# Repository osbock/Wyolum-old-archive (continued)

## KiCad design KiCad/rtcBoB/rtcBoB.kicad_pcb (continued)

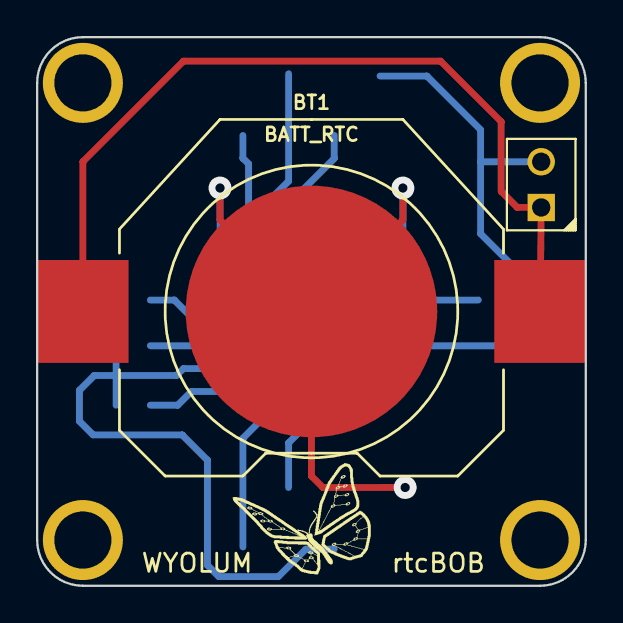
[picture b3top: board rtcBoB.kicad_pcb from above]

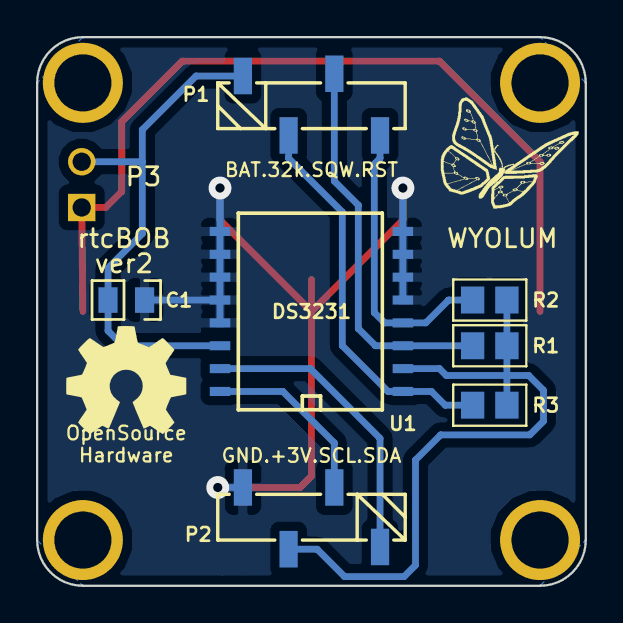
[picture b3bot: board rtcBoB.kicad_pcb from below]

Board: 2 copper layers, 30.5 x 30.5 mm, 15 parts (8 on the bottom side), 9 nets.

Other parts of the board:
G1, G1#2: Logo-WL3

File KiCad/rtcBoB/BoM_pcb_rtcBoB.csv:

"Id";"Designator";"Package";"Quantity";"Designation";"Supplier and ref";
1;"P3";"pin_strip_2";1;"CONN_2";;;
2;"U1";"DS3231";1;"DS3231";;;
3;"H4,H3,H2,H1";"vite_2mm5";4;"CONN_1";;;
4;"P1";"Sck-04-F-SMT";1;"CDOT1";;;
5;"P2";"Sck-04-F-SMT";1;"CDOT2";;;
6;"R1,R2,R3";"r_0805";3;"10k";;;
7;"C1";"c_0805";1;"100n";;;
8;"G1,G1";"Logo-WL3";2;"Logo-WL3";;;
9;"G***";"OSHW_6mm";1;"LOGO";;;
10;"BT1";"CR2032_SMD";1;"BATT_RTC";;;

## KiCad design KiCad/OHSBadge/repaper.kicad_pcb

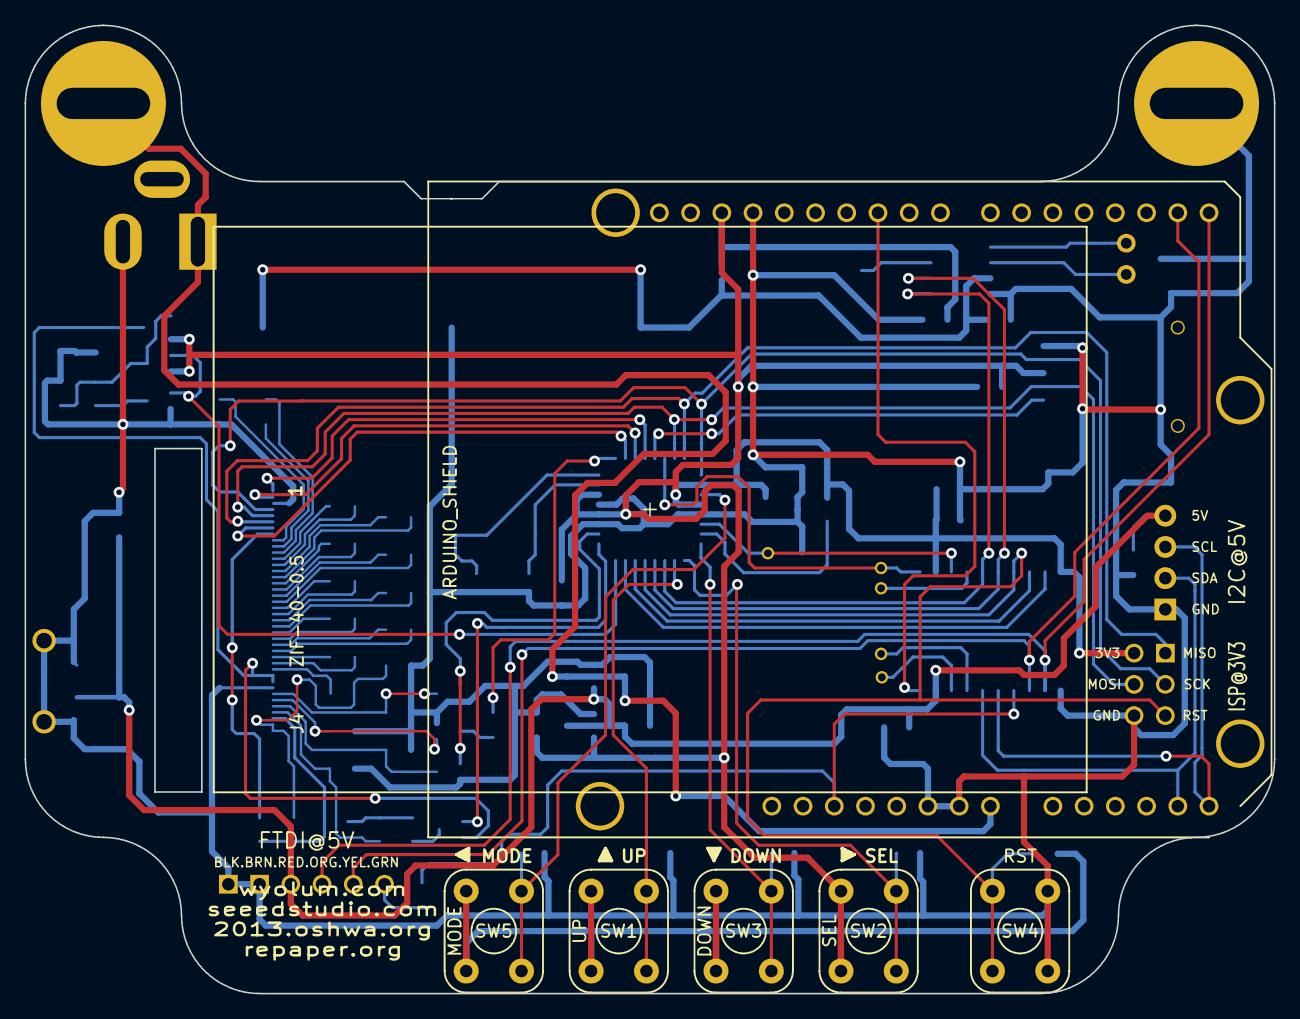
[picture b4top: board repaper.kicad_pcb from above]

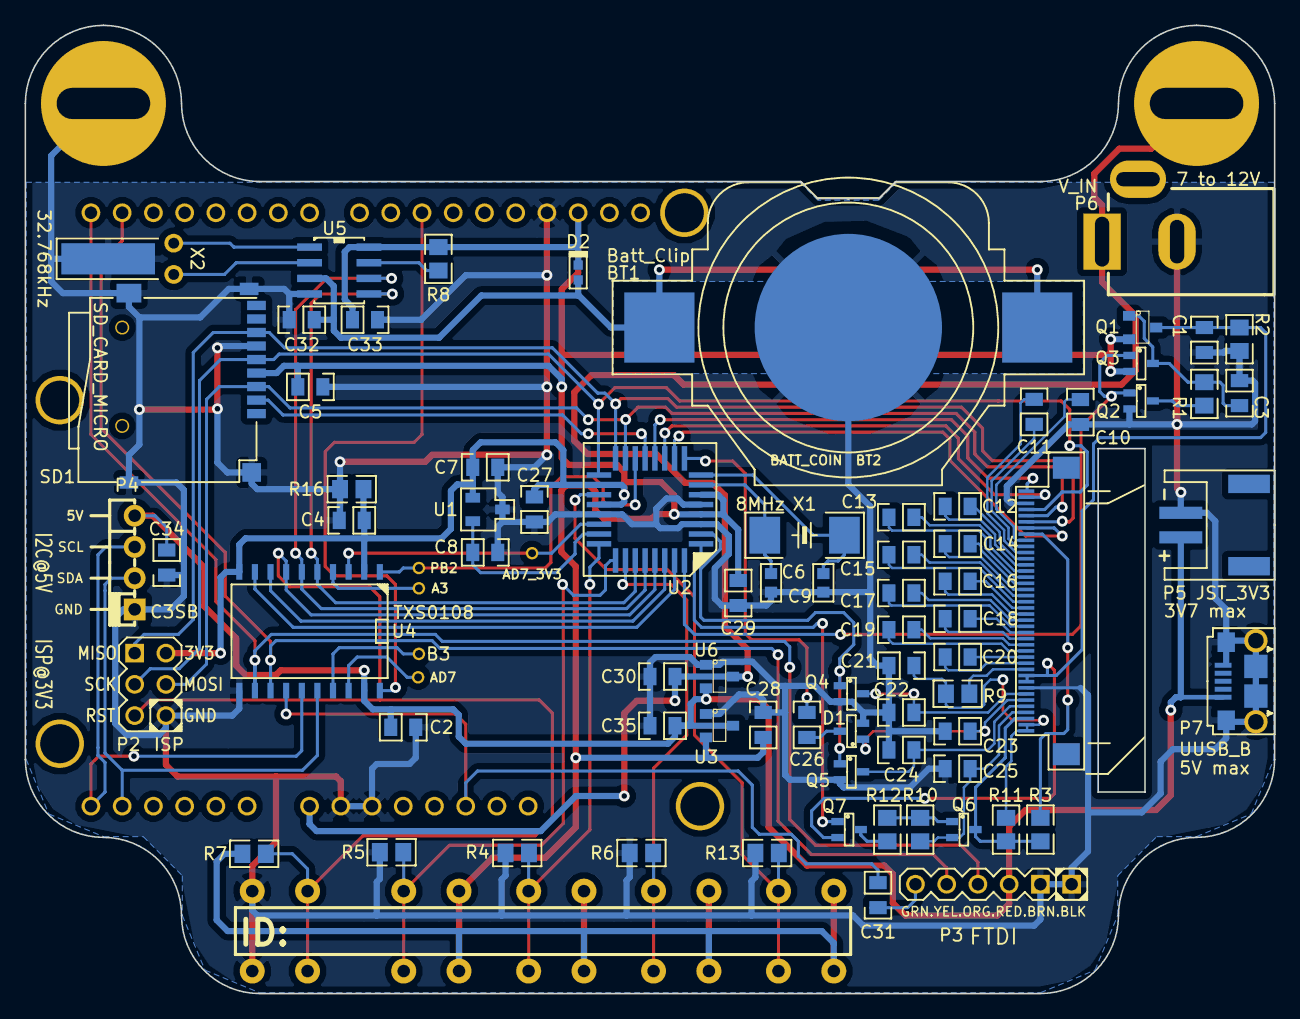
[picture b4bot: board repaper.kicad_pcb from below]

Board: 2 copper layers, 101.6 x 78.7 mm, 90 parts (80 on the bottom side), 78 nets.

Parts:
A3: I/O
AD7, AD7_3V3: I/O
B3: I/O
BT1: Batt_Clip; CR2450_SMD
BT2: BATT_COIN; CR2032
C1, C11, C12, C14, C17, C18, C19, C20, C24, C25, C28, C30, C35: 2.2u,16V; c_0805
C2, C3, C4, C5, C8, C26, C27, C29, C31, C32, C33, C34: 0.1u,16V; c_0805
C6, C9: 22pF; c_0603
C7: 1u,16V; c_0805
C10: 2.2u,10V; c_0805
C13, C15, C16, C22, C23: 2.2u,25V; c_0805
C21: 1u,10V; c_0805
D1: BAT54SW; SOT323
D2: DB2S20500L; d_VMD2
H1, H2: I/O; vite_3mm
J4: ZIF-40-0.5; ZIF-40-0.5-M_Hirose
P1: PCB
P2: ISP; Header_ISP
P3: FTDI; Header_FTDI
P4: C3SB; pin_strip_4-90
P5: JST_3V3; CONN_JST-2_SMD
P6: V_IN; JACK_ALIM
P7: UUSB_B; USB_B_Micro
PB2: I/O
Q1: DMG2301U-7; SOT23
Q2, Q4, Q5, Q6: 2N7002KW; SOT323
Q3, Q7: BSS84W; SOT323
R1, R2: 33k; r_0805
R3: 0R(NC); r_0805
R4, R5, R6, R7, R8, R13, R16: 10k; r_0805
R9: 2k; r_0805
R10, R11, R12: 100k; r_0805
SD1: SD_CARD_MICRO; SD_Micro
SHIELD1: ARDUINO_SHIELD; ARDUINO_SHIELD_040pins
SW1: UP; SW-PB
SW2: SEL; SW-PB
SW3: DOWN; SW-PB
SW4: RST; SW-PB
SW5: MODE; SW-PB
U1: MCP9700AT-E/TT; SOT23-3-Temp
U2: ATMEGA328-AU-ND; TQFP32
U3: MCP1700T-33; SOT23
U4: TXS0108; SO20L
U5: DS1307; SO8E
U6: MCP1702T-50; SOT23
X1: 8MHz; Xtal_SMD
X2: 32.768kHz; XTAL_3

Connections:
/3V3: C4.1, C5.1, C7.2, C27.2, C28.1, C29.1, C33.1, D2.2, P2.5, Q1.2, Q3.2, R7.2, R8.2, R16.2, SD1.4, SHIELD1.AREF, SW1.2, SW2.2, SW3.2, SW5.2, U1.1, U2.4, U2.6, U2.18, U2.20, U3.2, U4.2, U4.10, U5.8
//EPD_CS_3V3: J4.1, U2.12
//RESET_3V3: J4.7, U2.10
/AD7: AD7.1, U4.18
/AD7_3V3: AD7_3V3.1, U2.22, U4.3
/BATT_3V: BT1.+, C32.1, D2.1, U5.3
/BORDER: J4.38, Q6.3, R3.2, R11.1
/BORDER_CONTROL: Q7.1, U2.1
/BUSY_3V3: J4.2, U2.11
/C11M: C20.1, J4.28
/C11P: C20.2, J4.29
/C12M: C19.1, J4.26
/C12P: C19.2, J4.27
/C13M: C18.1, J4.24
/C13P: C18.2, J4.25
/C14M: C17.1, J4.22
/C14P: C17.2, J4.23
/C15M: C16.1, J4.20
/C15P: C16.2, J4.21
/C16M: C15.1, J4.18
/C16P: C15.2, J4.19
/C21M: C14.1, J4.16
/C21P: C14.2, J4.17
/C31M: C13.1, J4.14
/C31P: C13.2, J4.15
/C41M: C12.2, J4.13
/C41P: C12.1, J4.12
/C42M: C11.2, J4.11
/C42P: C11.1, J4.10
/DISCHARGE: Q4.1, Q5.1, U2.2
/DOWN: R4.2, SW3.1, U2.24
/DTR: C31.2, P3.6
/MODE: R13.2, SW5.1, U2.19
/PANEL_ON: Q2.1, Q3.1, U2.32
/PWM: C26.2, U2.9
/RST: C31.1, SHIELD1.RST, U4.14
/RST_3V3: P2.2, R7.1, SW4.2, U2.29, U4.7
/RXD: P3.4, SHIELD1.0, U4.12
/RXD_3V3: U2.30, U4.8
/SCL: P4.2, SHIELD1.AD5, U4.15
/SCL_3V3: U2.28, U4.6, U5.6
/SDA: P4.3, SHIELD1.AD4, U4.16
/SDA_3V3: U2.27, U4.5, U5.5
/SD_CS_3V3: SD1.2, U2.13
/SEL: R5.2, SW2.1, U2.25
/SPI_CLK_3V3: J4.4, P2.4, SD1.5, U2.17
/SPI_MISO_3V3: J4.6, P2.6, SD1.7, U2.16
/SPI_MOSI_3V3: J4.5, P2.3, SD1.3, U2.15
/SPI_SS: SHIELD1.10, U4.20
/SPI_SS_3V3: PB2.1, U2.14, U4.1
/SQW: R8.1, U5.7
/TEMPERATURE: C8.1, U1.2, U2.23
/TXD: P3.5, SHIELD1.1, U4.13
/TXD_3V3: U2.31, U4.9
/UP: R6.2, SW1.1, U2.26
/VCC5V: C2.1, C34.1, C35.1, P3.3, P4.1, P5.1, P7.1, U3.3, U4.19, U6.2
/VCC_T: C1.2, J4.31, J4.32, Q1.3, Q7.2, R2.1
/VCL: C10.2, J4.9
/VCOM: C21.2, J4.39, J4.40, R9.2, R11.2
/VCOM_DRIVER: J4.30, R9.1
/VDH: C24.1, J4.36, Q5.3
/VDL: C25.1, J4.37, Q6.2, R10.2
/VGH: C22.1, J4.34, Q4.3
/VGL: C23.1, D1.1, J4.35
/V_IN: C30.1, H1.1, P6.1, SHIELD1.V_IN, U6.3
GND: BT1.-, C1.1, C2.2, C3.1, C4.2, C5.2, C6.1, C7.1, C8.2, C9.1, C10.1, C21.1, C22.2, C23.2, C24.2, C25.2, C27.1, C28.2, C29.2, C30.2, C32.2, C33.2, C34.2, C35.2, D1.2, H2.1, J4.3, J4.33, P2.1, P3.1, P3.2, P4.4, P5.2, P6.2, P7.5, P7.T1, P7.T2, P7.T3, P7.T4, P7.T5, P7.T6, Q2.2, Q4.2, Q5.2, R2.2, R4.1, R5.1, R6.1, R13.1, R16.1, SD1.6, SD1.G1, SD1.G2, SD1.G3, SD1.G4, SHIELD1.GND1, SHIELD1.GND2, SHIELD1.GND3, SW4.1, U1.3, U2.3, U2.5, U2.21, U3.1, U4.11, U5.4, U6.1, X2.3
unnamed: Q2.3, R1.1
unnamed: B3.1, U4.17
unnamed: A3.1, U4.4
unnamed: C3.2, Q1.1, Q3.3, R1.2
unnamed: Q6.1, R10.1, R12.1
unnamed: Q7.3, R12.2
unnamed: C26.1, D1.3
unnamed: J4.8, R3.1
unnamed: U5.2, X2.2
unnamed: U5.1, X2.1
unnamed: C9.2, U2.8, X1.1
unnamed: C6.2, U2.7, X1.2

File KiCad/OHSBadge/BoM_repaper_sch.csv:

I/O	6	"A3 AD7 AD7_3V3 B3 PB2 U5/7"	I/O
BATT_COIN	1	"BT2"	CR2032	BATTERY LITHIUM COIN 3V 20MM	Lithium, 3V, 225mAh	CR2032	Panasonic - BSG	CR2032	Digikey	P189-ND
Batt_Clip	1	"BT1"	CR2450_SMD	HOLDER BATTERY COIN 20MM DIA THM	Coin Cell, Retainer	Coin, 20.0mm	Keystone Electronics	3003	Digikey	3003K-ND
22pF	2	"C6 C9"	c_0603	0603/0.1uF/16V
0.1u,16V	9	"C2 C4 C5 C27 C29 C31 C32 C33 C34"	c_0805	0603/0.1uF/16V
0.1u,16V	1	"C3"	c_0805	0402/0.1uF/16V/Y5V
0.1u,16V	1	"C8"	c_0805	0603/0.1uF/16V	DNP
0.1u,16V	1	"C26"	c_0805	0603/100n/16V/X7R
1u,16V	1	"C7"	c_0805	1u/10V/X7R
1u,10V	1	"C21"	c_0805	1u/10V/X7R
2.2u,16V	1	"C1"	c_0805	0805/2.2u/10V/Y5V
2.2u,10V	1	"C10"	c_0805	0805/2.2u/10V/Y5V
2.2u,16V	9	"C11 C12 C14 C17 C18 C19 C20 C24 C25"	c_0805	0805/2.2u/16V/Y5V
2.2u,25V	5	"C13 C15 C16 C22 C23"	c_0805	0805/2.2u/25V/Y5V
2.2u,16V	3	"C28 C30 C35"	c_0805	0805/2.2uF/16V/Y5V
DB2S20500L	1	"D2"	d_VMD2
BAT54SW	1	"D1"	SOT323
OSHW	1	"G4"	OSHW_logo
repaper	1	"G3"	repaper_logo
seeed	1	"G2"	seeed
WYO	1	"G1"	wyo_logo
I/O	2	"H1 H2"	vite_3mm
ZIF-40-0.5	1	"J4"	ZIF-40-0.5-M_Hirose
JST_3V3	1	"P5"	CONN_JST-2_SMD
FTDI	1	"P3"	Header_FTDI
ISP	1	"P2"	Header_ISP
V_IN	1	"P6"	JACK_ALIM	CONN POWER JACK MALE 2.5MM CLSD	Jack, Male	2.5mm ID, 5.5mm OD	CUI Inc	PJ-002B	Digikey	CP-002B-ND
PCB	1	"P1"	PCB
C3SB	1	"P4"	pin_strip_4-90
UUSB_B	1	"P7"	USB_B_Micro
DMG2301U-7	1	"Q1"	SOT23
2N7002KW	4	"Q2 Q4 Q5 Q6"	SOT323
BSS84W	2	"Q3 Q7"	SOT323
0R(NC)	1	"R3"	r_0805	0402/0R/5%/(NC)	DNP
2k	1	"R9"	r_0805	0603/2k/5%
10k	7	"R4 R5 R6 R7 R8 R13 R16"	r_0805	0402/0R/5%
33k	1	"R1"	r_0805	0402/33K/5%
33k	1	"R2"	r_0805	0402/33k/5%/(NC)	DNP
100k	3	"R10 R11 R12"	r_0805	0402/100k/5%
SD_CARD_MICRO	1	"SD1"	SD_Micro
ARDUINO_SHIELD	1	"SHIELD1"	ARDUINO_SHIELD_040pins
UP	1	"SW1"	SW-PB
SEL	1	"SW2"	SW-PB
DOWN	1	"SW3"	SW-PB
RST	1	"SW4"	SW-PB
MODE	1	"SW5"	SW-PB
TXS0108	1	"U4"	SO20L
DS1307	1	"U5"	SO8E
MCP1700T-33	1	"U3"	SOT23	MCP1700T-3302E/TT
MCP1702T-50	1	"U6"	SOT23	MCP1700T-3302E/TT
MCP9700AT-E/TT	1	"U1"	SOT23-3-Temp
ATMEGA328-AU-ND	1	"U2"	TQFP32
32.768kHz	1	"X2"	XTAL_3
8MHz	1	"X1"	Xtal_SMD

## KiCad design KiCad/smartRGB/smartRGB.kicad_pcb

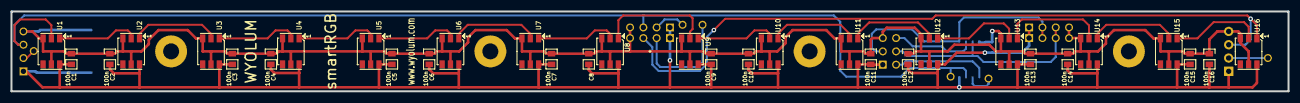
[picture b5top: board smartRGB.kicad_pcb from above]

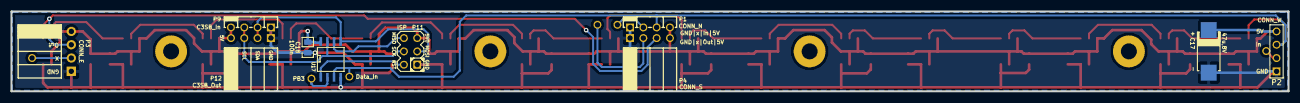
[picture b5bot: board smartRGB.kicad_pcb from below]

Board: 2 copper layers, 243.8 x 15.2 mm, 53 parts (12 on the bottom side), 28 nets.

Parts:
C1, C2, C3, C4, C5, C6, C7, C8, C9, C10, C11, C12, C13, C14, C15, C16, C18: 100n; c_0805
C17: 47u,8V; c_2917
P1: CONN_N
P2: CONN_W
P3: CONN_E; CONN_S
P4: CONN_S
P5, P6, P7, P8: CONN_1; pad
P9: C3SB_In; CONN_N
P10: Data_In; pad
P11: ISP; Header_ISP
P12: C3SB_Out; CONN_S
PB3: PB3; pad
PCB1: CONN_1; PCB
S1, S2, S3, S4: CONN_1; Screw
U1, U2, U3, U4, U5, U6, U7, U8, U9, U10, U11, U12, U13, U14, U15, U16: RGB_WS2811
U17: ATTINY45-20SU; SO8N

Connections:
/D_02: U1.1, U2.2
/D_03: U2.1, U3.2
/D_04: U3.1, U4.2
/D_05: U4.1, U5.2
/D_06: U5.1, U6.2
/D_07: U6.1, U7.2
/D_08: U7.1, U8.2
/D_09: U8.1, U9.2
/D_10: U9.1, U10.2
/D_11: U10.1, U11.2
/D_12: U11.1, U12.2
/D_13: U12.1, U13.2
/D_14: U13.1, U14.2
/D_15: U14.1, U15.2
/D_16: U15.1, U16.2
/Data_Out: P3.2, P4.3, U16.1
/SlaveController/5V: C1.2, C2.2, C3.2, C4.2, C5.2, C6.2, C7.2, C8.2, C9.2, C10.2, C11.2, C12.2, C13.2, C14.2, C15.2, C16.2, C17.1, C18.1, P1.4, P2.4, P3.1, P4.4, P9.1, P11.2, P12.1, U1.3, U1.5, U2.3, U2.5, U3.3, U3.5, U4.3, U4.5, U5.3, U5.5, U6.3, U6.5, U7.3, U7.5, U8.3, U8.5, U9.3, U9.5, U10.3, U10.5, U11.3, U11.5, U12.3, U12.5, U13.3, U13.5, U14.3, U14.5, U15.3, U15.5, U16.3, U16.5, U17.8
/SlaveController/Data_In: P1.3, P2.3, P10.1, U1.2, U17.3
/SlaveController/MISO: P11.1, U17.6
/SlaveController/MOSI_SDA: P9.3, P11.4, P12.3, U17.5
/SlaveController/PB3: PB3.1, U17.2
/SlaveController/RST: P11.5, U17.1
/SlaveController/SCK_SCL: P9.2, P11.3, P12.2, U17.7
GND: C1.1, C2.1, C3.1, C4.1, C5.1, C6.1, C7.1, C8.1, C9.1, C10.1, C11.1, C12.1, C13.1, C14.1, C15.1, C16.1, C17.2, C18.2, P1.1, P2.1, P3.4, P4.1, P9.4, P11.6, P12.4, U1.6, U2.6, U3.6, U4.6, U5.6, U6.6, U7.6, U8.6, U9.6, U10.6, U11.6, U12.6, U13.6, U14.6, U15.6, U16.6, U17.4
unnamed: P4.2, P8.1
unnamed: P1.2, P5.1
unnamed: P2.2, P6.1
unnamed: P3.3, P7.1

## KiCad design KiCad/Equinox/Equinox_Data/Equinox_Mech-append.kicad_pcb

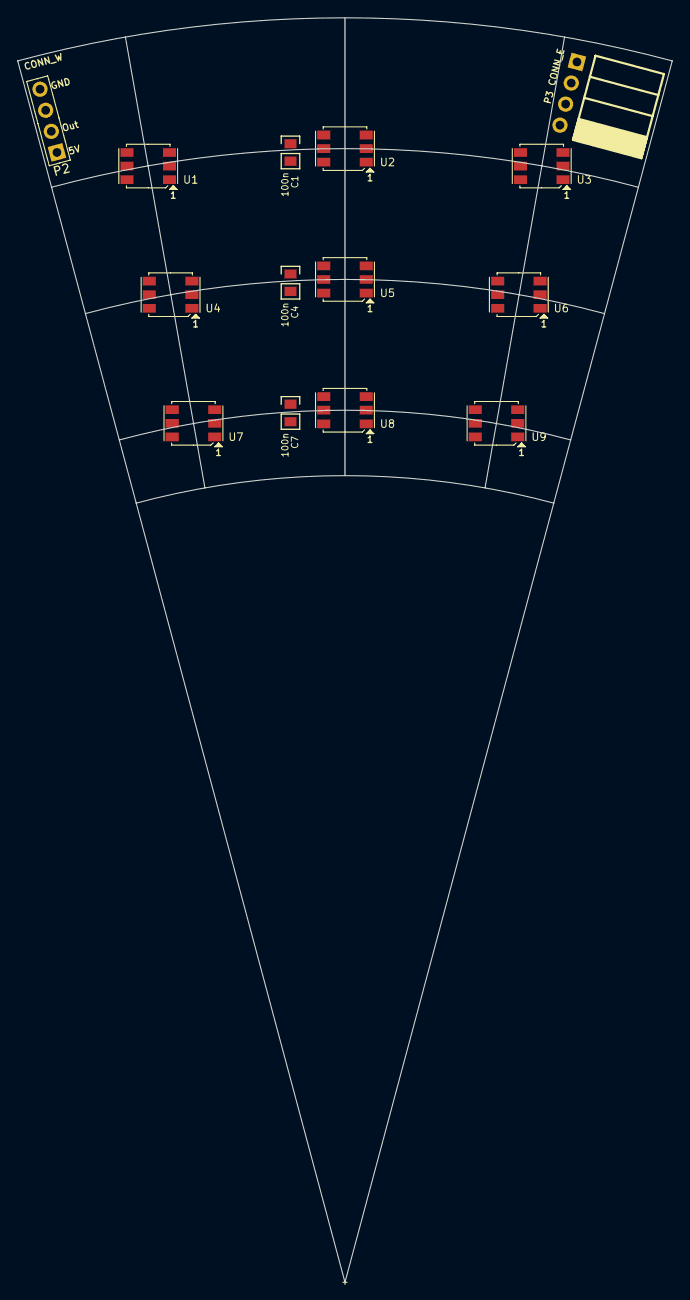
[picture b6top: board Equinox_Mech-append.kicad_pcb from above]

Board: 2 copper layers, 76.3 x 147.3 mm, 15 parts (0 on the bottom side), 6 nets, no tracks yet.

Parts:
C1, C4, C7: 100n; c_0805
P2: CONN_W; CONN_E
P3: CONN_E; CONN_S
PCB1: CONN_1; PCB
U1, U2, U3, U4, U5, U6, U7, U8, U9: RGB_WS2811

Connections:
/5V: P2.1, P3.1, U1.3, U1.5, U2.3, U2.5, U3.3, U3.5, U4.3, U4.5, U5.3, U5.5, U6.3, U6.5, U7.3, U7.5, U8.3, U8.5, U9.3, U9.5
/D_15: U1.2, U2.2, U3.2, U4.2, U5.2, U6.2, U7.2, U8.2, U9.2
/D_16: U1.1, U2.1, U3.1, U4.1, U5.1, U6.1, U7.1, U8.1, U9.1
/Data_Out: P2.2, P3.2
/SlaveController/5V: C1.2, C4.2, C7.2
GND: C1.1, C4.1, C7.1, P2.4, P3.4, U1.6, U2.6, U3.6, U4.6, U5.6, U6.6, U7.6, U8.6, U9.6

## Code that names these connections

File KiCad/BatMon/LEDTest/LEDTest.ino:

/*
B = PD2 = 2
F = PD3 = 3
A = PD4 = 4
E = PD5 = 5
D = PD6 = 6
DP = PD7= 7
C = PB0 = 8
G = PB1 = 9
d1 = PB2 = 10
d2 = PB3 = 11
d3 = PB4 = 12
d4 = PB5 = 13
*/
unsigned char digits[][7] = {
  {4,2,8,5,6,3,0}, // zero
  {2,8,0,0,0,0,0}, // one
  {4,2,9,6,5,0,0}, // two
  {4,2,9,8,6,0,0}, //three
  {3,2,9,8,0,0,0}, //four
  {4,3,9,8,6,0,0}, //five
  {4,3,5,6,8,9,0}, //six
  {4,2,8,0,0,0,0}, //seven
  {2,3,4,5,6,8,9}, //eight
  {3,4,9,2,8,0,0}, //nine
};

int displayRegister =9999; // this is read and displayed constantly  
void setup() {
  Serial.begin(9600);
  // put your setup code here, to run once:
  for (int i = 2; i < 14; i++){
    pinMode(i,OUTPUT);
  }
  for (int x = 10 ;x < 14; x++)
    digitalWrite(x,LOW);
}
long lastMillis =0;
#define INTERVAL 200
void loop() {
  long currentMillis = millis();
  if (currentMillis-lastMillis > INTERVAL){
     lastMillis = currentMillis;
     int reading = analogRead(A0);
     Serial.println(reading);
     displayRegister=(int)(((long)analogRead(A0)*1000L)/540L);
     
  }
   runDisplay();
 }
 
void runDisplay(){
  displayNumber(displayRegister);
  
}
void displayNumber(int i){
  if (i > 9999) return;
   blankdisplay();
   displayDigit(i %10,0);
   blankdisplay();
   displayDigit((i%100/10),1);
   blankdisplay();
   displayDigit((i%1000)/100,2);
   blankdisplay();
   displayDigit((i%10000)/1000,3);
   blankdisplay();


}
void blankdisplay(){
  for (int i =2; i < 10; i++)
    digitalWrite(i,LOW);
  for(int x = 10; x < 14; x++)
    digitalWrite(x, LOW);
}
void displayDigit(int num, int col){
  if (num > 9999) return;
  if (col > 3) return;
 
  digitalWrite(col+10,HIGH);
  if (col == 2)
    digitalWrite(7,HIGH);
  for (int i =0; (i< 8) ; i++){
    if (digits[num][i] ==0) return;
    digitalWrite(digits[num][i],HIGH);
  }
}

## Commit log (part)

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2012-06-21 pulse - final gerber files created. BoM finalized
2012-06-22 aLaMode - working on adding in FTDI USB functionality.
2012-06-23 pulse - software done. check in pulse_fader folder.
2012-06-25 pulse - SW mod.
2012-06-25 aLaMode - complete. Final Gerbers and BoM.
2012-06-30 pulse - minor digikey BoM update
2012-07-12 aLaMode - v2, added +5V0, +3V3 and GND headers for Analog Inputs
2012-07-12 BatMon - v2, revised board layout, moved some components around
2012-07-20 fixed double updating
2012-07-21 Name in Lights - NiL - minor library mods
2012-07-21 Added script to set time to whatever for glamour shots. Also does mirror image.
2012-07-23 undefined ATMEGA for production
2012-07-25 p.u.l.s.e - minor changes to the code to make it pulse better. Also, ND pin is set low by default.
2012-07-27 p.u.l.s.e. - updated the sketch
2012-07-28 aLaMode_v2 done. Gerbers generated. But need a final look-over before we send to seeed.
2012-08-07 Change P1 header to female, 4Uconnector example .05" jumper shunts for power, u6 enable RPI interface
2012-08-14 Added I2GPS sketches, Updated TimeZ
2012-08-18 I2GPS codes
2012-08-22 Carduino added few Images. Added sketch Folder
2012-08-23 removed some jumpers
2012-09-05 I2GPS Client test script added.
2012-09-08 I've put in an experimental diming. Problem is that it does not work with fading (when time changes).
    Feel free to test it out. Add the line
    #define DIM
    to ClockTHREE_04. Inc and Dec increase and decrease brightness.
2012-10-15 BPC Pump connector board
2012-10-19 BPC minor silk screen mod.
2012-11-20 i2gps_v1 added Datasheet pdf and images
2012-11-23 C3Jr_v2 added new BoM for retail clock (full assembly at seeed) and files needed for Laser parts
2012-11-23 AlaMode minor mods.
2012-11-25 Added Spec Sheets
2012-11-27 uControl - added schematic page for Interfaces
2012-11-28 uControl schematic development. To Do decide on control pins for Pump, Pressure and Valve
2012-11-30 uControl schematic in progress
2012-11-30 Nb_LED - not final, some clean up pending
2012-12-01 Nb_adapter - added a small adapter for converting 5x2 header to 10x2
2012-12-03 uControl added schematic PDF and some data sheets
2012-12-07 uControl some minor edits to schematic
2012-12-17 uControl added some pdf datasheets
2012-12-20 uControl Footprints work in progress
2012-12-22 uControl Footprints in progress
2012-12-23 uControl Justin, check the Footprints - print the uControl.brd file
2012-12-23 uControl minor mods to footprints
2012-12-25 uControl footprints done. working on initial board layout
2012-12-26 uControl - minor mods to .brd and .mod files.
2012-12-27 uControl footprint layout almost done.
2012-12-28 uControl changed to Thru Hole design. Basic parts laid out. No tracks yet.
2012-12-29 uControl track layout complete. Needs to be checked.
2012-12-30 uControl - board layout done. Needs a good check now.
2012-12-31 uControl track layout done. need to clean up silk legend.
2013-01-01 uControl - Board seems done. Needs some final checks before sending for prototype
2013-01-02 uControl : looks done. Final reviews and checks left. Gerbers ready.
2013-01-03 uControl v1 Prototype complete. Gerbers generated, BoM finalized.
2013-01-04 uControl correction ATMega8 to ATMega328P. changed sch, pcb and BoM files. Also, simplified Manifold design.
2013-01-05 C3Jr_v2_nil couple of images added
2013-01-05 RowGB complete. Need to check PCB layout
2013-01-07 uControl - minor mod to footprint library
2013-01-07 RowGB - modified footprints library to correct path to 3d files.
2013-01-11 KiCad folder, some clean up.
2013-01-16 uControl : Manifold modified - deeper hole for 1/4"-28 UNF Barb taps
2013-01-24 added Xavitech pump documentation.
2013-01-25 uControl : flipped pump connector, added Capacitor for Pump, etc. Also added 3D model of Flow Meter
2013-01-29 Nb_v03 BoM revised.
2013-02-04 Nb_v3 : v3 final Gerbers.
2013-02-05 uControl : added additional footprint for flowmeter. Added 5V regulator for Ras-Pi.
2013-02-07 uControl : some board changes, and added folder for uControl box/case
2013-02-08 uControl 5V breakout board for supply to Ras-Pi from 12V barrel socket.
2013-02-09 uControl : Acrylic box design on single page
2013-02-09 added unit tests for uControl
2013-02-11 TiM layout seems done. Board cleanup required.
2013-02-13 TiM : Need to add legend for stacking connectors.
2013-02-14 TiM : Booya !! Final checks required before prototype boards.
2013-02-15 TiM minor legend clean up
2013-02-18 RowGB and TIM : Final Gerbers generated. Ready for prototype run.
2013-02-18 RasPi_RTC : started new project folder.
2013-02-21 RowGB - updated the Attiny slave controller schematic sheet
2013-02-22 RasPi_RTC : Booya ! to be checked.
2013-02-23 RasPi_RTC : renamed EPOCH. created final Gerber files (some mods in Legend, tracks etc). Created seeed format BOM. Added Logos to Legend.
2013-03-04 uControl : Modified Acrylic box/case files
2013-03-06 smartRGB : x16 row of WS2811 LED Pixels with ATTiny85 controller
2013-03-08 Nachbau_v03 modified BOM Files.
2013-03-10 Nachbau_v03 modified Silk Legend to identify v03
2013-03-12 Changed name of folder (RasPi_RTC to RasPi_Epoch)
2013-03-14 OHSBadge (repaper) converted EPD reference schematic to KiCad format (needs a lot of work, though).
2013-03-15 RasPi_EPOCH : added two projects - Epoch_smd for DS3231 SMD board, and Epoch_TH for DS1307 TH board.
2013-03-15 RasPi_Epoch : Epoch_TH done. Need to verify the circuit and layout.
2013-03-21 Raspi_EPOCH - boards renamed as EPOCH_smd and EPOCH_th. Final gerber plots and BoM files ready.
2013-03-22 EPaper Badge - added seeed reference circuit.
2013-03-23 reverted to original strandtest from github (with minor mod)
2013-03-24 work in progress, cleaning up repaper reference schematic
2013-03-27 repaper badge - schematic work in progress
2013-03-28 new smartRGB folder. Moved files from old OHSBadge to here.
2013-03-29 OHSBadge - Controller to EPD pin connections assigned. Need to check 5V out from Digital Port 10
2013-03-30 OHSBadge - started basic PCB layout
2013-03-31 OHSBadge - smoe edits to footprint libs
2013-04-01 OHSBadge - original design renamed as repaper_dumb. creating a new Schematic with ATMega included.
2013-04-02 OHSBadge : added 328P, and full Arduino shield. See Board outline for lanyard looping option.
2013-04-04 OHSBadge working on board layout.
2013-04-06 Kevin's smartRGB library using Adafruit NeoPixel
2013-04-07 OHSBadge, Schematic update, added coin batt, JST connector, 3V3 selector.
2013-04-08 OHSBadge - getting some basic track layout done
2013-04-09 OHSBadge - track layout done. Added thru hole switches. All SMD parts are on solder side now.
2013-04-09 OHSBadge Switches were reversed (corrected). Added 4th switch (Mode). SPI header pads were mirrored when footprint was flipped over. Moved Voltage SEL P6 to make space for 4th switch.
2013-04-11 OHSBadge : track layout complete. Power section revamped - please check. Some parts need new footprints - Resonator (instead of crystal).
2013-04-12 OHSBadge : added logos. added 12V barrel socket. changed Xtal and Xtal Capacitors footprint. Part2 - internet is acting crappy today.
2013-04-12 OHSBadge : added logos. added 12V barrel socket. changed Xtal and Xtal Capacitors footprint. Part4 - internet is acting crappy today.
2013-04-12 OHSBadge - geberated gerbers to check/verify on OHSPark.com
2013-04-13 OHSBadge-Part2 : Completed. Initial gerbers made for verification. Final checks pending. Added more 3D parts.
2013-04-13 OHSBadge-Part4 : Completed. Initial gerbers made for verification. Final checks pending. Added more 3D parts.
2013-04-13 OHSBadge-Part6 : Completed. Initial gerbers made for verification. Final checks pending. Added more 3D parts.
2013-04-14 OHSBadge : working on the silk legends. Everything else seems almost done.
2013-04-15 OHSBadge : Completed. Gerbers ready for prototyping.
2013-04-15 OHSBadge : a minor clean up of silk legends.
2013-04-16 OHSBadge : checking the layout one final time. Some minor mods made.
2013-04-17 OHSBadge : Final for prototyping.
2013-04-17 OHSBadge : Added file with 3D call outs for OHSBadge. BoM update for 2450 battery/holder. 2450 to 2032 adapter.
2013-04-21 rtcBoB : v2 all SMD. BoM is pending.
2013-04-22 OHSBadge : Corrected Battery Retainer P/N in BoM
2013-04-23 C3v2 : minor mod to BoM file
2013-05-13 OHSBadge : swapped Tx and Rx signals based on seeed feedback.
2013-05-18 added Screen example for TiM
2013-05-24 OHSBadge : created separate folder. Put HW interrupts INT0 and INT1 on switches. Moved uSD card to edge etc. OHS logo with LED heartbeat
2013-05-24 OHSBadge : created separate folder. Put HW interrupts INT0 and INT1 on switches. Moved uSD card to edge etc. OHS logo with LED heartbeat. Part 3
2013-05-31 OHSBadge : Coin Batt slot made wider. Increased [-] pad mask.
2013-06-02 pre disk crash commit
2013-06-03 OHSBadge : v3 Final Prototype. Added PDF Files.
2013-06-05 OHSBadge : BADGEr_v3 Final Prototype. Added PDF Files. Minor mods.
2013-06-07 OHSBadge : BADGEr_v3 Final Prototype. push buttons changed to SMD. Added SMD ON switch for BATTERY. Centered P-Buttons with EPD.
2013-06-07 OHSBadge : BADGEr_v3 Final Prototype. Added Slide Switch 3D Module
2013-06-11 OHSBadge : BADGEr_v4. Disconnect V_IN between Shield and Badge
2013-06-13 OHSBadge : BADGEr_v4. Added DNP to unpopulated parts on schematic. Max. Page turns BATT warning on Back Legend. Breakout Pads for unused Shield headers
2013-06-14 AlaMode_v3 : Updated BOM. Added resistors for GPS Rx.
2013-06-14 AlaMode_v3 : minor clean up, nothing new here.
2013-06-14 BADGEr - added MOSFET data sheet
2013-06-18 AlaMode_v3 : BoM updated - added Bumpon feet.
2013-07-08 uControl : added Zephyr datasheet
2013-07-08 uControl_v2 : renamed the schematic file
2013-07-15 OHSBadge : BADGEr_v4. ICSP Pin 1 legend error corrected. Fresh Gerbers/PDF's generated
2013-07-17 OHSBadge : BADGEr_v4. 2450 Batt Page turns reduced to 100. Fresh Gerbers/PDF's generated
2013-08-13 uControl_v2 : schematic work in progress
2013-08-14 added scad files for manifold
2013-08-14 uControl_v2 schematic progression
2013-08-15 uControl_v2 : added the schematic PDF
2013-08-16 removed rouned corners
2013-08-17 added manifold to uControl_v2 directory
2013-08-17 uControl_v2 progress : Pump 3d added
2013-08-18 uControl_v2 : 3D modules for Flow, Pump, Valve, Pr sensors
2013-08-21 uControl_v2 - laying out the parts on the board
2013-08-22 uControl_v2 : Farm enclosure files added.
2013-08-23 uControl_v2 : minor mods
2013-08-24 uControl_v2 : working on getting PiPower 3D in to the board to allow proper placement.
2013-08-25 uControl_v2 : Moved parts around - Pr Gauge, RasPi etc
2013-08-26 uControl_v2 : Ready to stary layout once RasPi and Gage orientation is finalized
2013-09-01 uControl_v2 : working on track layout. half way through.
2013-09-11 uControl_v2 : track layout in progress. 3 tracks left to go.
2013-09-19 uControl_v2 : track layout complete. Silk Legend in progress
2013-09-23 OHSBadge : BADGEr_v4. Dimensional drawings created - pdf and dxf
2013-09-26 uControl_v2 working on modifying new pump
2013-09-28 uControl_v2 : Copper fill zones, Legend done. Moved LED's so they are visible (were located under PiPower earlier), and other mods.
2013-09-28 added connector data sheet
2013-09-30 uControl_v2 : Modified PiPower outline (56mm wide)
2013-12-02 added some data sheets
2013-12-05 uControl_v3 created new folder for uControl using BBB instead of Ras-Pi (_v2) #1 Base files
2013-12-05 uControl_v3 created new folder for uControl using BBB instead of Ras-Pi (_v2) #3 3D Modules
2013-12-07 uControl_v2 added pdf files for PCB
2013-12-07 uControl_v3 added BBB 3D module
2013-12-11 AlaMode_v3 added Board dimensions
2013-12-16 Defined keep out zone
2013-12-21 uControl_v3 work in progress
2013-12-29 uCv3 added 5V<>3V discrete converter with break out pads. Final checks to be done
2013-12-31 uCv3 working on the BoM
2014-02-19 aLaMode_v3 added 3D files
2014-07-21 added an images
2016-03-06 Migrating wiki contents from Google Code
